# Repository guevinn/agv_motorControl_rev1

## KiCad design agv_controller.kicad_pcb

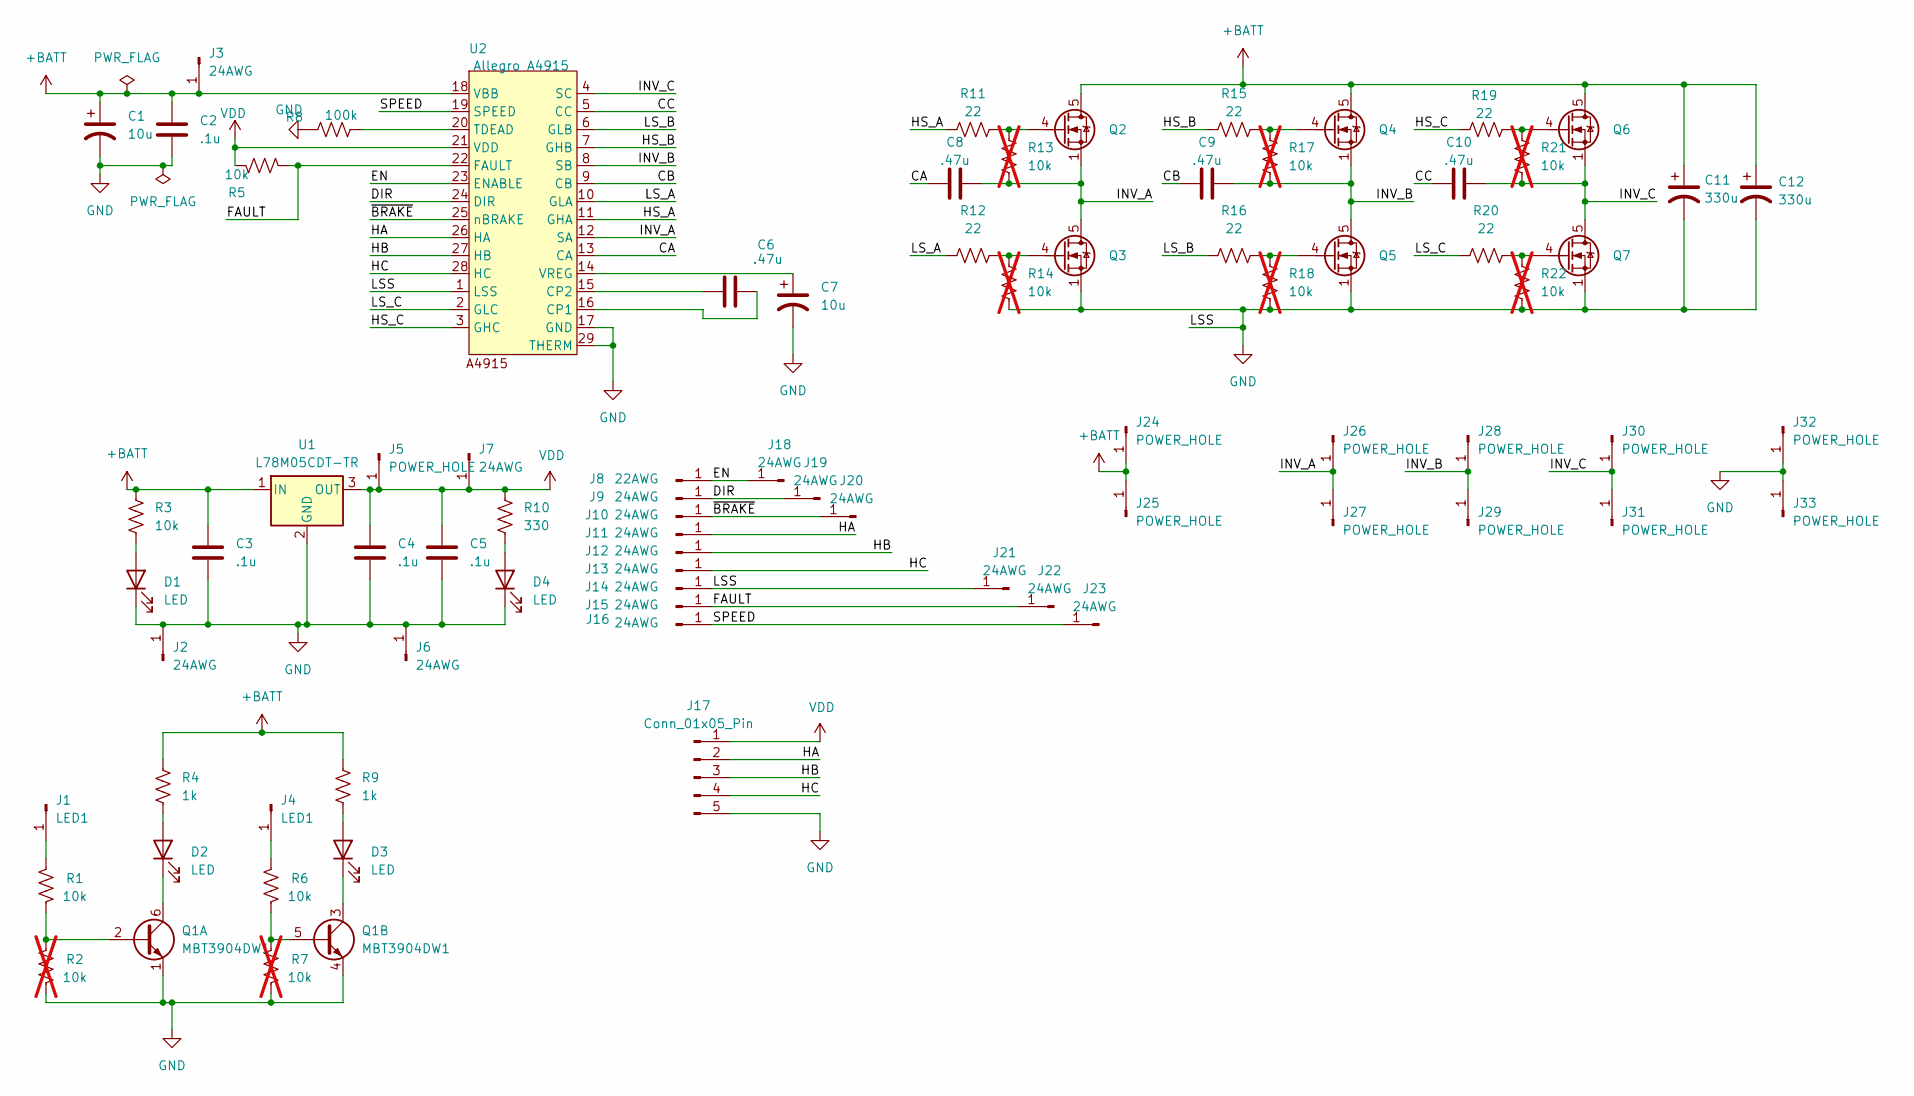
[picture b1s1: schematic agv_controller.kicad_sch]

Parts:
C1, C7: 10u; CP_Radial_D10.0mm_P5.00mm
C2, C3, C4, C5: .1u; C_0603_1608Metric
C6, C8, C9, C10: .47u; C_0603_1608Metric
C11, C12: 330u; CP_Radial_D10.0mm_P5.00mm
D1, D2, D3, D4: LED; LED_0603_1608Metric
J1, J4: LED1; SolderWire-0.5sqmm_1x01_D0.9mm_OD2.1mm
J2, J3, J6, J7, J9, J10, J11, J12, J13, J14, J15, J16, J18, J19, J20, J21, J22, J23: 24AWG; SolderWire-0.5sqmm_1x01_D0.9mm_OD2.1mm
J5, J24, J25, J26, J27, J28, J29, J30, J31, J32, J33: POWER_HOLE; SolderWire-4sqmm_1x01_D3mm_OD6mm
J8: 22AWG; SolderWire-0.5sqmm_1x01_D0.9mm_OD2.1mm
J17: Conn_01x05_Pin; JST_EH_B5B-EH-A_1x05_P2.50mm_Vertical
Q1: MBT3904DW1; SOT-363_SC-70-6
Q2, Q3, Q4, Q5, Q6, Q7: BSC028N06LS3; TDSON-8-1
R1, R3, R5, R6: 10k; R_0603_1608Metric
R2, R7, R13, R14, R17, R18, R21, R22: 10k; R_0603_1608Metric; not fitted
R4, R9: 1k; R_0603_1608Metric
R8: 100k; R_0603_1608Metric
R10: 330; R_0603_1608Metric
R11, R12, R15, R16, R19, R20: 22; R_0603_1608Metric
U1: L78M05CDT-TR; TO-220-3_Vertical
U2: Allegro A4915; HTSSOP-28-1EP_4.4x9.7mm_P0.65mm_EP2.75x6.2mm_ThermalVias

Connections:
+BATT: C1.1, C2.1, C3.1, C11.1, C12.1, J3.1, J24.1, J25.1, Q2.5 (D), Q4.5 (D), Q6.5 (D), R3.2, R4.2, R9.2, U1.1 (IN), U2.18 (VBB)
/CA: C8.2, U2.13 (CA)
/CB: C9.2, U2.9 (CB)
/CC: C10.2, U2.5 (CC)
/DIR: J9.1, J19.1, U2.24 (DIR)
/EN: J8.1, J18.1, U2.23 (ENABLE)
/FAULT: J15.1, J22.1, R5.1, U2.22 (FAULT)
/HA: J11.1, J17.2, U2.26 (HA); also elsewhere on the board
/HS_A: R11.1, U2.11 (GHA)
/HS_B: R15.1, U2.7 (GHB)
/HS_C: R19.1, U2.3 (GHC)
/INV_A: C8.1, J26.1, J27.1, Q2.1 (S), Q2.2 (S), Q2.3 (S), Q3.5 (D), R13.1, U2.12 (SA)
/INV_B: C9.1, J28.1, J29.1, Q4.1 (S), Q4.2 (S), Q4.3 (S), Q5.5 (D), R17.1, U2.8 (SB)
/INV_C: C10.1, J30.1, J31.1, Q6.1 (S), Q6.2 (S), Q6.3 (S), Q7.5 (D), R21.1, U2.4 (SC)
/LS_A: R12.1, U2.10 (GLA)
/LS_B: R16.1, U2.6 (GLB)
/LS_C: R20.1, U2.2 (GLC)
/SPEED: J16.1, J23.1, U2.19 (SPEED)
/~BRAKE: J10.1, J20.1, U2.25 (nBRAKE)
GND: C1.2, C2.2, C3.2, C4.2, C5.2, C7.2, C11.2, C12.2, D1.1 (K), D4.1 (K), J2.1, J6.1, J14.1, J17.5, J21.1, J32.1, J33.1, Q1.1 (E1), Q1.4 (E2), Q3.1 (S), Q3.2 (S), Q3.3 (S), Q5.1 (S), Q5.2 (S), Q5.3 (S), Q7.1 (S), Q7.2 (S), Q7.3 (S), R2.2, R7.2, R8.1, R14.1, R18.1, R22.1, U1.2 (GND), U2.1 (LSS), U2.17 (GND), U2.29 (THERM)
unnamed: D1.2 (A), R3.1
unnamed: D2.2 (A), R4.1
unnamed: D2.1 (K), Q1.6 (C1)
unnamed: D3.2 (A), R9.1
unnamed: D3.1 (K), Q1.3 (C2)
unnamed: D4.2 (A), R10.1
unnamed: J1.1, R1.1
unnamed: J4.1, R6.1
unnamed: Q1.2 (B1), R1.2, R2.1
unnamed: Q1.5 (B2), R6.2, R7.1
unnamed: Q2.4 (G), R11.2, R13.2
unnamed: Q3.4 (G), R12.2, R14.2
unnamed: Q4.4 (G), R15.2, R17.2
unnamed: Q5.4 (G), R16.2, R18.2
unnamed: Q6.4 (G), R19.2, R21.2
unnamed: Q7.4 (G), R20.2, R22.2
unnamed: C6.2, U2.16 (CP1)
unnamed: C6.1, U2.15 (CP2)
unnamed: R8.2, U2.20 (TDEAD)
unnamed: C7.1, U2.14 (VREG)
VDD: C4.1, C5.1, J5.1, J7.1, J17.1, R5.2, R10.2, U1.3 (OUT), U2.21 (VDD)

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
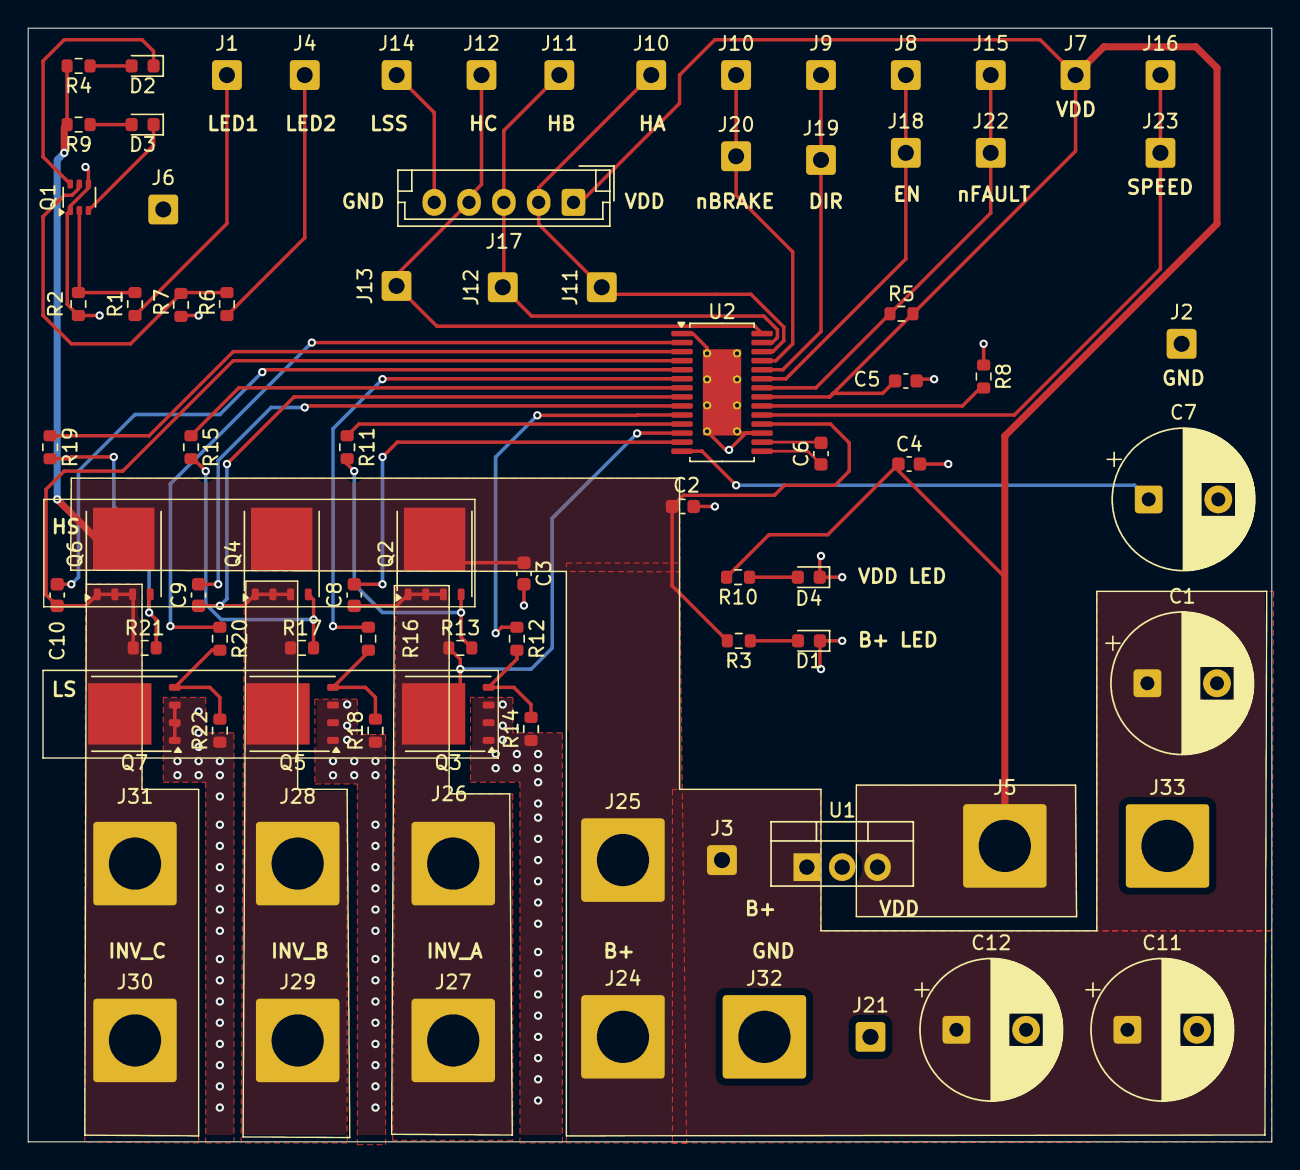
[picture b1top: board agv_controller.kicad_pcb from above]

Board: 2 copper layers, 89.3 x 80.0 mm, 83 parts (0 on the bottom side), 43 nets.

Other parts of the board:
J10#2, J11#2, J12#2: 24AWG; SolderWire-0.5sqmm_1x01_D0.9mm_OD2.1mm

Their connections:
/HA: J10#2.1; also elsewhere on the board

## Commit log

2026-03-25 Finished schematic
2026-03-27 Finished schematic with LEDs and fixed ERC
2026-03-27 Swapped connectors to fix PCB net issues
2026-03-30 Made initial component placement before starting routing
2026-03-31 ERC passing PCB
2026-03-31 Added labels all over silk screen for easier assembly
2026-03-31 Generate gerbers and drill files
